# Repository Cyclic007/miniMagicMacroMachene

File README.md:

# MiniMagicMacroMachene

This is a 3x3 macropad that uses black cherry keyswitches and a raspberry pi pico 1w made to be used with AutoHotKey

## Total Price $50.18 USD

| Qty | Name                                | Datasheet                                                                               | source                                                                                       | unit cost | Total cost |
|-----|-------------------------------------|-----------------------------------------------------------------------------------------|----------------------------------------------------------------------------------------------|-----------|------------|
| 1   | RaspberryPi_Pico 1w                  | https://datasheets.raspberrypi.com/pico/pico-datasheet.pdf                              | https://www.pishop.us/product/raspberry-pi-pico-wh-pre-soldered-headers/                     | 13.95     | 13.95      |
| 9   | 1N4148                              | https://assets.nexperia.com/documents/data-sheet/1N4148_1N4448.pdf                      | https://www.digikey.com/en/products/detail/onsemi/1N4148/458603                              | 0.1       | 7.38       |
| 9   | Cherry MX2A Black 60g Linear Switch | https://cherry.saas.contentserv.com/admin/rest/document/30?ContextIDs=15343&Language=36 | https://mechanicalkeyboards.com/products/cherry-mx2a-black-60g-linear?variant=48014721286444 | 0.4       | 8.79       |
| 1   | PCB                                 |                                                                                         | https://www.pcbway.com/QuickOrderOnline.aspx                                                 | 20.06     | 20.06      |

There is a battery thing I am going to use but I tried to find the datasheet and price and couldn't

also the case will be painted and butified phisicly after it is printed

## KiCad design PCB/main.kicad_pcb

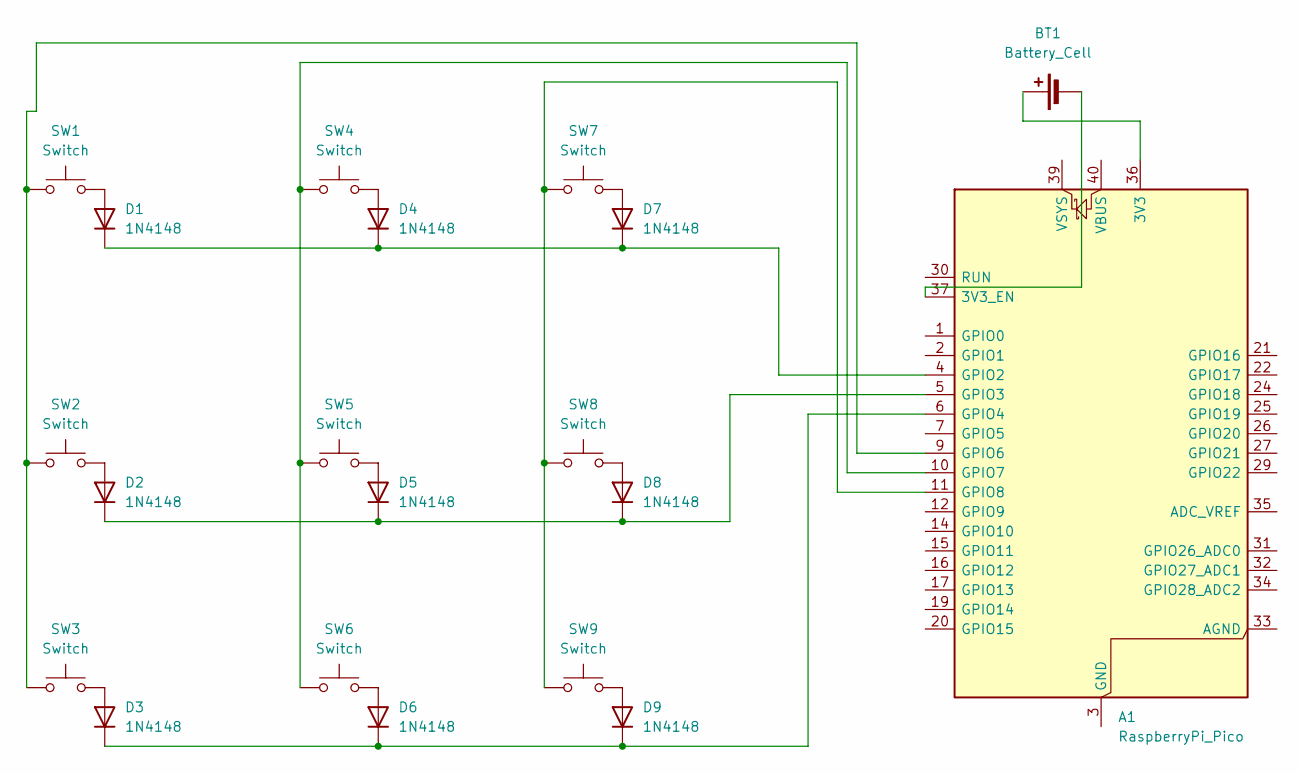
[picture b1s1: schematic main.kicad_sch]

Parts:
A1: RaspberryPi_Pico; RaspberryPi_Pico_Common_Unspecified
BT1: Battery_Cell
D1, D2, D3, D4, D5, D6, D7, D8, D9: 1N4148; D_DO-35_SOD27_P7.62mm_Horizontal
SW1, SW2, SW3, SW4, SW5, SW6, SW7, SW8, SW9: Switch; MX_PCB_1.00u

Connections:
unnamed: A1.3 (GND), A1.8 (GND), A1.13 (GND), A1.18 (GND), A1.23 (GND), A1.28 (GND), A1.38 (GND)
unnamed: A1.4 (GPIO2), D1.1 (K), D4.1 (K), D7.1 (K)
unnamed: A1.5 (GPIO3), D2.1 (K), D5.1 (K), D8.1 (K)
unnamed: A1.6 (GPIO4), D3.1 (K), D6.1 (K), D9.1 (K)
unnamed: A1.9 (GPIO6), SW1.1, SW2.1, SW3.1
unnamed: A1.10 (GPIO7), SW4.1, SW5.1, SW6.1
unnamed: A1.11 (GPIO8), SW7.1, SW8.1, SW9.1
unnamed: A1.36 (3V3), BT1.1 (+)
unnamed: A1.37 (3V3_EN), BT1.2 (-)
unnamed: D1.2 (A), SW1.2
unnamed: D2.2 (A), SW2.2
unnamed: D3.2 (A), SW3.2
unnamed: D4.2 (A), SW4.2
unnamed: D5.2 (A), SW5.2
unnamed: D6.2 (A), SW6.2
unnamed: D7.2 (A), SW7.2
unnamed: D8.2 (A), SW8.2
unnamed: D9.2 (A), SW9.2

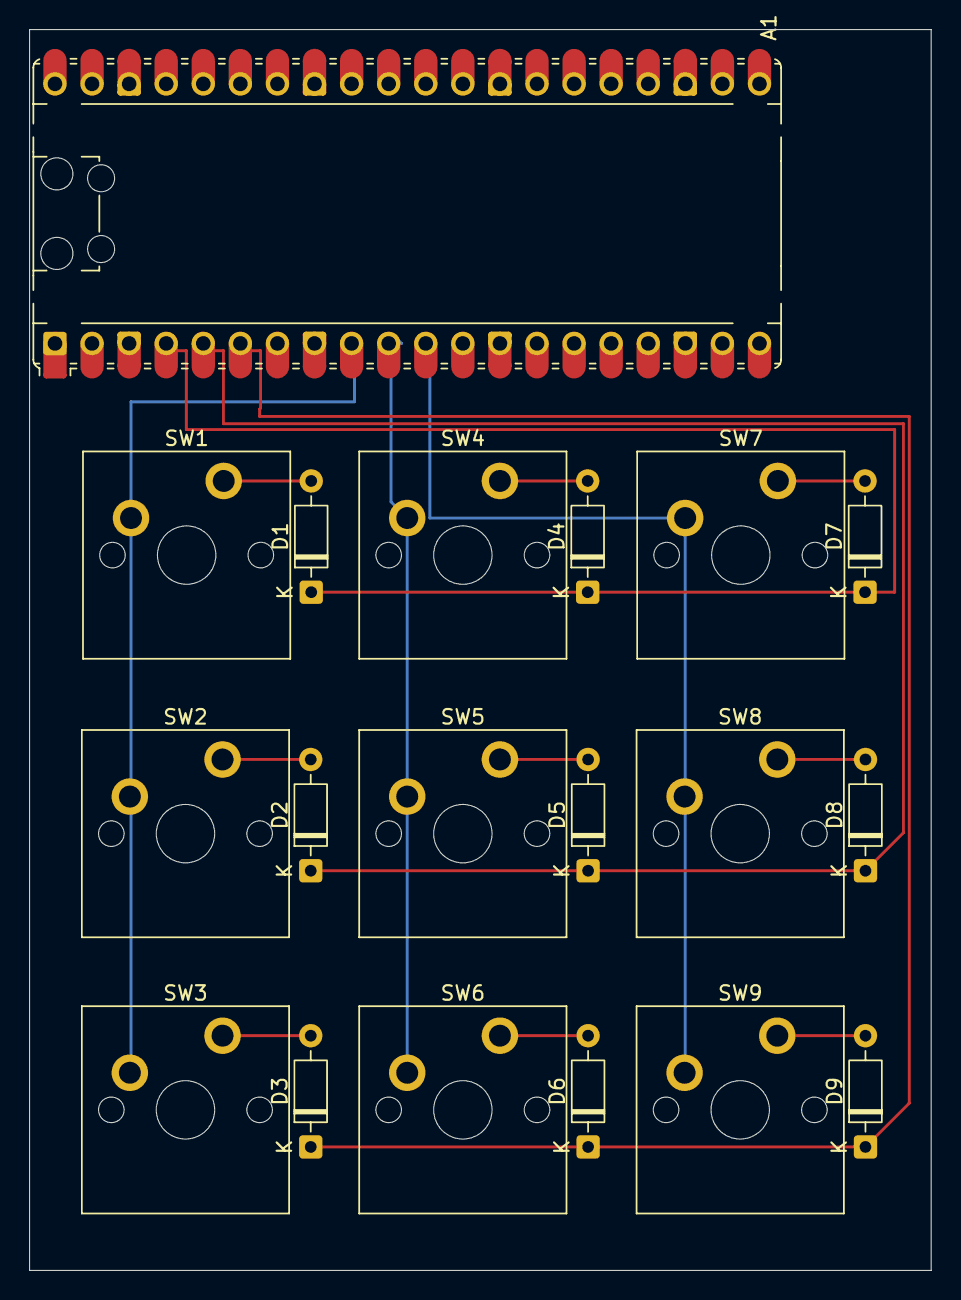
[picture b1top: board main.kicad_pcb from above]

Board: 2 copper layers, 61.8 x 85.0 mm, 19 parts (0 on the bottom side), 16 nets.

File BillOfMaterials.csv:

"Reference","Qty","Name","DNP","Exclude from BOM","Exclude from Board","Footprint","Datasheet","source","unit cost","Total cost"
"A1","1","RaspberryPi_Pico 2","","","","Module:RaspberryPi_Pico_Common_Unspecified","https://datasheets.raspberrypi.com/pico/pico-datasheet.pdf","https://www.pishop.us/product/raspberry-pi-pico-wh-pre-solde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","13.95","13.95"
"D1,D2,D3,D4,D5,D6,D7,D8,D9","9","1N4148","","","","Diode_THT:D_DO-35_SOD27_P7.62mm_Horizontal","https://assets.nexperia.com/documents/data-sheet/1N4148_1N4448.pdf","https://www.digikey.com/en/products/detail/onsemi/1N4148/458603","0.1","7.38"
"SW1,SW2,SW3,SW4,SW5,SW6,SW7,SW8,SW9","9","Cherry MX2A Black 60g Linear Switch","","","","ScottoKeebs_MX:MX_PCB_1.00u","https://cherry.saas.contentserv.com/admin/rest/document/30?C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","https://mechanicalkeyboards.com/products/cherry-mx2a-black-6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","0.4","8.79"
"","1","PCB","","","","","","https://www.pcbway.com/QuickOrderOnline.aspx","20.06","20.06"

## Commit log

2025-05-16 first
2025-05-16 add JOURNAL.md
2025-05-16 start JORNAL
2025-05-16 adding model
2025-05-16 made PCB and updated Jornal
2025-05-16 setup stuff for PCBway
2025-05-16 finished PCB
2025-05-16 add BOM
2025-05-16 makeing strides on case
2025-05-17 Update sym-lib-table
2025-05-17 tryed to make case
2025-05-17 made shell for pcb
2025-05-17 cleaning
2025-05-17 documentation things
2025-05-19 fixed pcb
2025-05-19 added new case model
2025-05-19 QMK stuff
2025-05-19 geting ready
2025-05-19 moveing things around
2025-05-19 adding BOM
2025-05-20 fixed problem wirh scamatic
2025-05-28 firmwere
2025-05-28 finishFirmwere
